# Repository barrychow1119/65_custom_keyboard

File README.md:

# Custom 65% Keyboard

Two-board design: passive key matrix + RP2040 controller.

## keyboard-main (key board)
- 306 × 97 mm, 2 layers, 1.6 mm, HASL lead-free
- 68 keys, Kailh MX hotswap, SOD-123F diodes, 4 stabilisers
- 16 cols × 5 rows → 30-pin 0.5 mm FFC
- Traces 0.127 mm, vias 0.6/0.3 mm
- Components on F.Cu (board mounts flipped in case)

## controller (RP2040 board)
- Not started

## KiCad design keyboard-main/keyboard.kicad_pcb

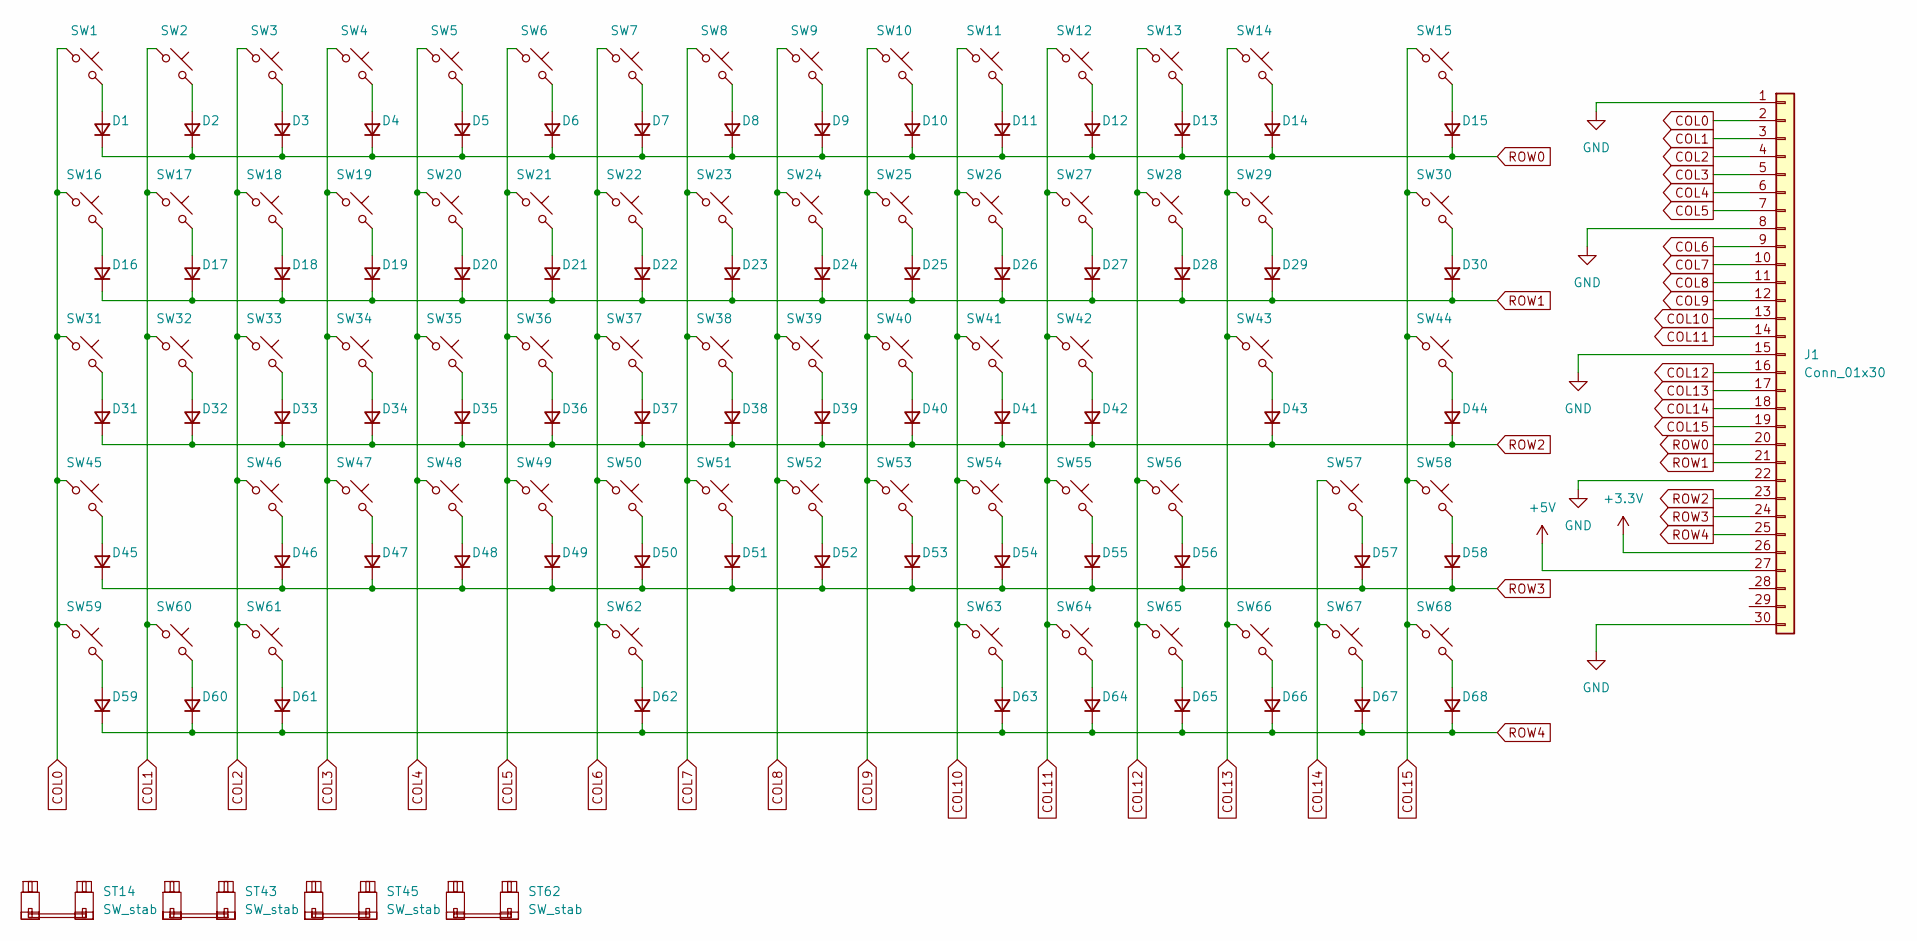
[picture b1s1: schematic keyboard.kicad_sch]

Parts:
D1, D2, D3, D4, D5, D6, D7, D8, D9, D10, D11, D12, D13, D14, D15, D16, D17, D18, D19, D20, D21, D22, D23, D24, D25, D26, D27, D28, D29, D30, D31, D32, D33, D34, D35, D36, D37, D38, D39, D40, D41, D42, D43, D44, D45, D46, D47, D48, D49, D50, D51, D52, D53, D54, D55, D56, D57, D58, D59, D60, D61, D62, D63, D64, D65, D66, D67, D68: D; D_SOD-123F
J1: Conn_01x30; Hirose_FH12-30S-0.5SH_1x30-1MP_P0.50mm_Horizontal
ST14, ST43, ST45: SW_stab; Stabilizer_Cherry_MX_2.00u
ST62: SW_stab; Stabilizer_Cherry_MX_6.25u
SW1, SW2, SW3, SW4, SW5, SW6, SW7, SW8, SW9, SW10, SW11, SW12, SW13, SW15, SW17, SW18, SW19, SW20, SW21, SW22, SW23, SW24, SW25, SW26, SW27, SW28, SW30, SW32, SW33, SW34, SW35, SW36, SW37, SW38, SW39, SW40, SW41, SW42, SW44, SW46, SW47, SW48, SW49, SW50, SW51, SW52, SW53, SW54, SW55, SW57, SW58, SW63, SW64, SW65, SW66, SW67, SW68: SW_Push; SW_Hotswap_Kailh_MX_1.00u
SW14: SW_Push; SW_Hotswap_Kailh_MX_2.00u
SW16, SW29: SW_Push; SW_Hotswap_Kailh_MX_1.50u
SW31, SW56: SW_Push; SW_Hotswap_Kailh_MX_1.75u
SW43, SW45: SW_Push; SW_Hotswap_Kailh_MX_2.25u
SW59, SW60, SW61: SW_Push; SW_Hotswap_Kailh_MX_1.25u
SW62: SW_Push; SW_Hotswap_Kailh_MX_6.25u

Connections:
+3.3V: J1.26
+5V: J1.27
COL0: J1.2, SW1.1, SW16.1, SW31.1, SW45.1, SW59.1
COL1: J1.3, SW2.1, SW17.1, SW32.1, SW60.1
COL2: J1.4, SW3.1, SW18.1, SW33.1, SW46.1, SW61.1
COL3: J1.5, SW4.1, SW19.1, SW34.1, SW47.1
COL4: J1.6, SW5.1, SW20.1, SW35.1, SW48.1
COL5: J1.7, SW6.1, SW21.1, SW36.1, SW49.1
COL6: J1.9, SW7.1, SW22.1, SW37.1, SW50.1, SW62.1
COL7: J1.10, SW8.1, SW23.1, SW38.1, SW51.1
COL8: J1.11, SW9.1, SW24.1, SW39.1, SW52.1
COL9: J1.12, SW10.1, SW25.1, SW40.1, SW53.1
COL10: J1.13, SW11.1, SW26.1, SW41.1, SW54.1, SW63.1
COL11: J1.14, SW12.1, SW27.1, SW42.1, SW55.1, SW64.1
COL12: J1.16, SW13.1, SW28.1, SW56.1, SW65.1
COL13: J1.17, SW14.1, SW29.1, SW43.1, SW66.1
COL14: J1.18, SW57.1, SW67.1
COL15: J1.19, SW15.1, SW30.1, SW44.1, SW58.1, SW68.1
GND: J1.1, J1.8, J1.15, J1.22, J1.30
unnamed: D1.2 (A), SW1.2
unnamed: D2.2 (A), SW2.2
unnamed: D3.2 (A), SW3.2
unnamed: D4.2 (A), SW4.2
unnamed: D5.2 (A), SW5.2
unnamed: D6.2 (A), SW6.2
unnamed: D7.2 (A), SW7.2
unnamed: D8.2 (A), SW8.2
unnamed: D9.2 (A), SW9.2
unnamed: D10.2 (A), SW10.2
unnamed: D11.2 (A), SW11.2
unnamed: D12.2 (A), SW12.2
unnamed: D13.2 (A), SW13.2
unnamed: D14.2 (A), SW14.2
unnamed: D15.2 (A), SW15.2
unnamed: D16.2 (A), SW16.2
unnamed: D17.2 (A), SW17.2
unnamed: D18.2 (A), SW18.2
unnamed: D19.2 (A), SW19.2
unnamed: D20.2 (A), SW20.2
unnamed: D21.2 (A), SW21.2
unnamed: D22.2 (A), SW22.2
unnamed: D23.2 (A), SW23.2
unnamed: D24.2 (A), SW24.2
unnamed: D25.2 (A), SW25.2
unnamed: D26.2 (A), SW26.2
unnamed: D27.2 (A), SW27.2
unnamed: D28.2 (A), SW28.2
unnamed: D29.2 (A), SW29.2
unnamed: D30.2 (A), SW30.2
unnamed: D31.2 (A), SW31.2
unnamed: D32.2 (A), SW32.2
unnamed: D33.2 (A), SW33.2
unnamed: D34.2 (A), SW34.2
unnamed: D35.2 (A), SW35.2
unnamed: D36.2 (A), SW36.2
unnamed: D37.2 (A), SW37.2
unnamed: D38.2 (A), SW38.2
unnamed: D39.2 (A), SW39.2
unnamed: D40.2 (A), SW40.2
unnamed: D41.2 (A), SW41.2
unnamed: D42.2 (A), SW42.2
unnamed: D43.2 (A), SW43.2
unnamed: D44.2 (A), SW44.2
unnamed: D45.2 (A), SW45.2
unnamed: D46.2 (A), SW46.2
unnamed: D47.2 (A), SW47.2
unnamed: D48.2 (A), SW48.2
unnamed: D49.2 (A), SW49.2
unnamed: D50.2 (A), SW50.2
unnamed: D51.2 (A), SW51.2
unnamed: D52.2 (A), SW52.2
unnamed: D53.2 (A), SW53.2
unnamed: D54.2 (A), SW54.2
unnamed: D55.2 (A), SW55.2
unnamed: D56.2 (A), SW56.2
unnamed: D57.2 (A), SW57.2
unnamed: D58.2 (A), SW58.2
unnamed: D59.2 (A), SW59.2
unnamed: D60.2 (A), SW60.2
unnamed: D61.2 (A), SW61.2
unnamed: D62.2 (A), SW62.2
unnamed: D63.2 (A), SW63.2
unnamed: D64.2 (A), SW64.2
unnamed: D65.2 (A), SW65.2
unnamed: D66.2 (A), SW66.2
unnamed: D67.2 (A), SW67.2
unnamed: D68.2 (A), SW68.2
ROW0: D1.1 (K), D2.1 (K), D3.1 (K), D4.1 (K), D5.1 (K), D6.1 (K), D7.1 (K), D8.1 (K), D9.1 (K), D10.1 (K), D11.1 (K), D12.1 (K), D13.1 (K), D14.1 (K), D15.1 (K), J1.20
ROW1: D16.1 (K), D17.1 (K), D18.1 (K), D19.1 (K), D20.1 (K), D21.1 (K), D22.1 (K), D23.1 (K), D24.1 (K), D25.1 (K), D26.1 (K), D27.1 (K), D28.1 (K), D29.1 (K), D30.1 (K), J1.21
ROW2: D31.1 (K), D32.1 (K), D33.1 (K), D34.1 (K), D35.1 (K), D36.1 (K), D37.1 (K), D38.1 (K), D39.1 (K), D40.1 (K), D41.1 (K), D42.1 (K), D43.1 (K), D44.1 (K), J1.23
ROW3: D45.1 (K), D46.1 (K), D47.1 (K), D48.1 (K), D49.1 (K), D50.1 (K), D51.1 (K), D52.1 (K), D53.1 (K), D54.1 (K), D55.1 (K), D56.1 (K), D57.1 (K), D58.1 (K), J1.24
ROW4: D59.1 (K), D60.1 (K), D61.1 (K), D62.1 (K), D63.1 (K), D64.1 (K), D65.1 (K), D66.1 (K), D67.1 (K), D68.1 (K), J1.25

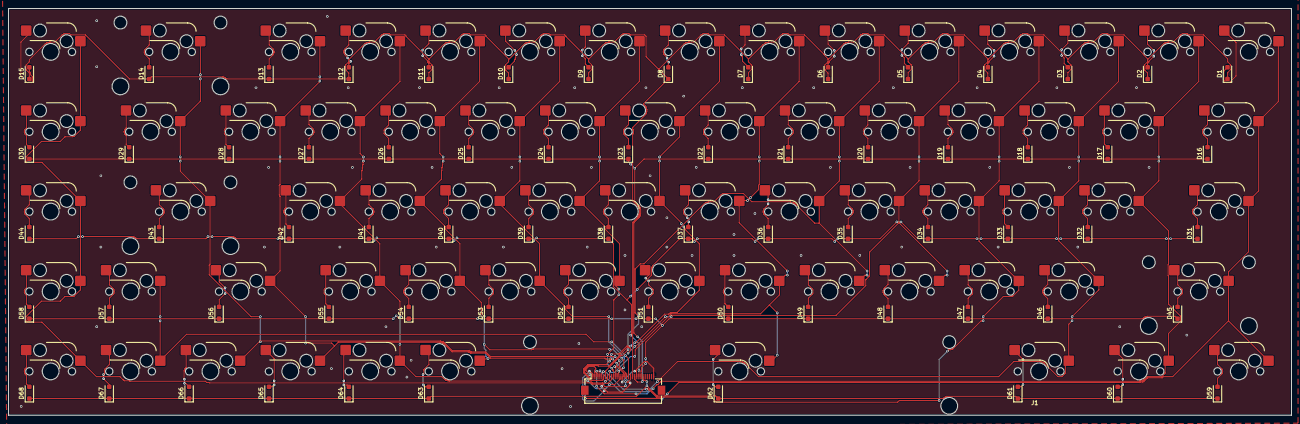
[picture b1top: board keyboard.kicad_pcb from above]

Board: 2 copper layers, 306.0 x 97.0 mm, 141 parts (72 on the bottom side), 90 nets.
